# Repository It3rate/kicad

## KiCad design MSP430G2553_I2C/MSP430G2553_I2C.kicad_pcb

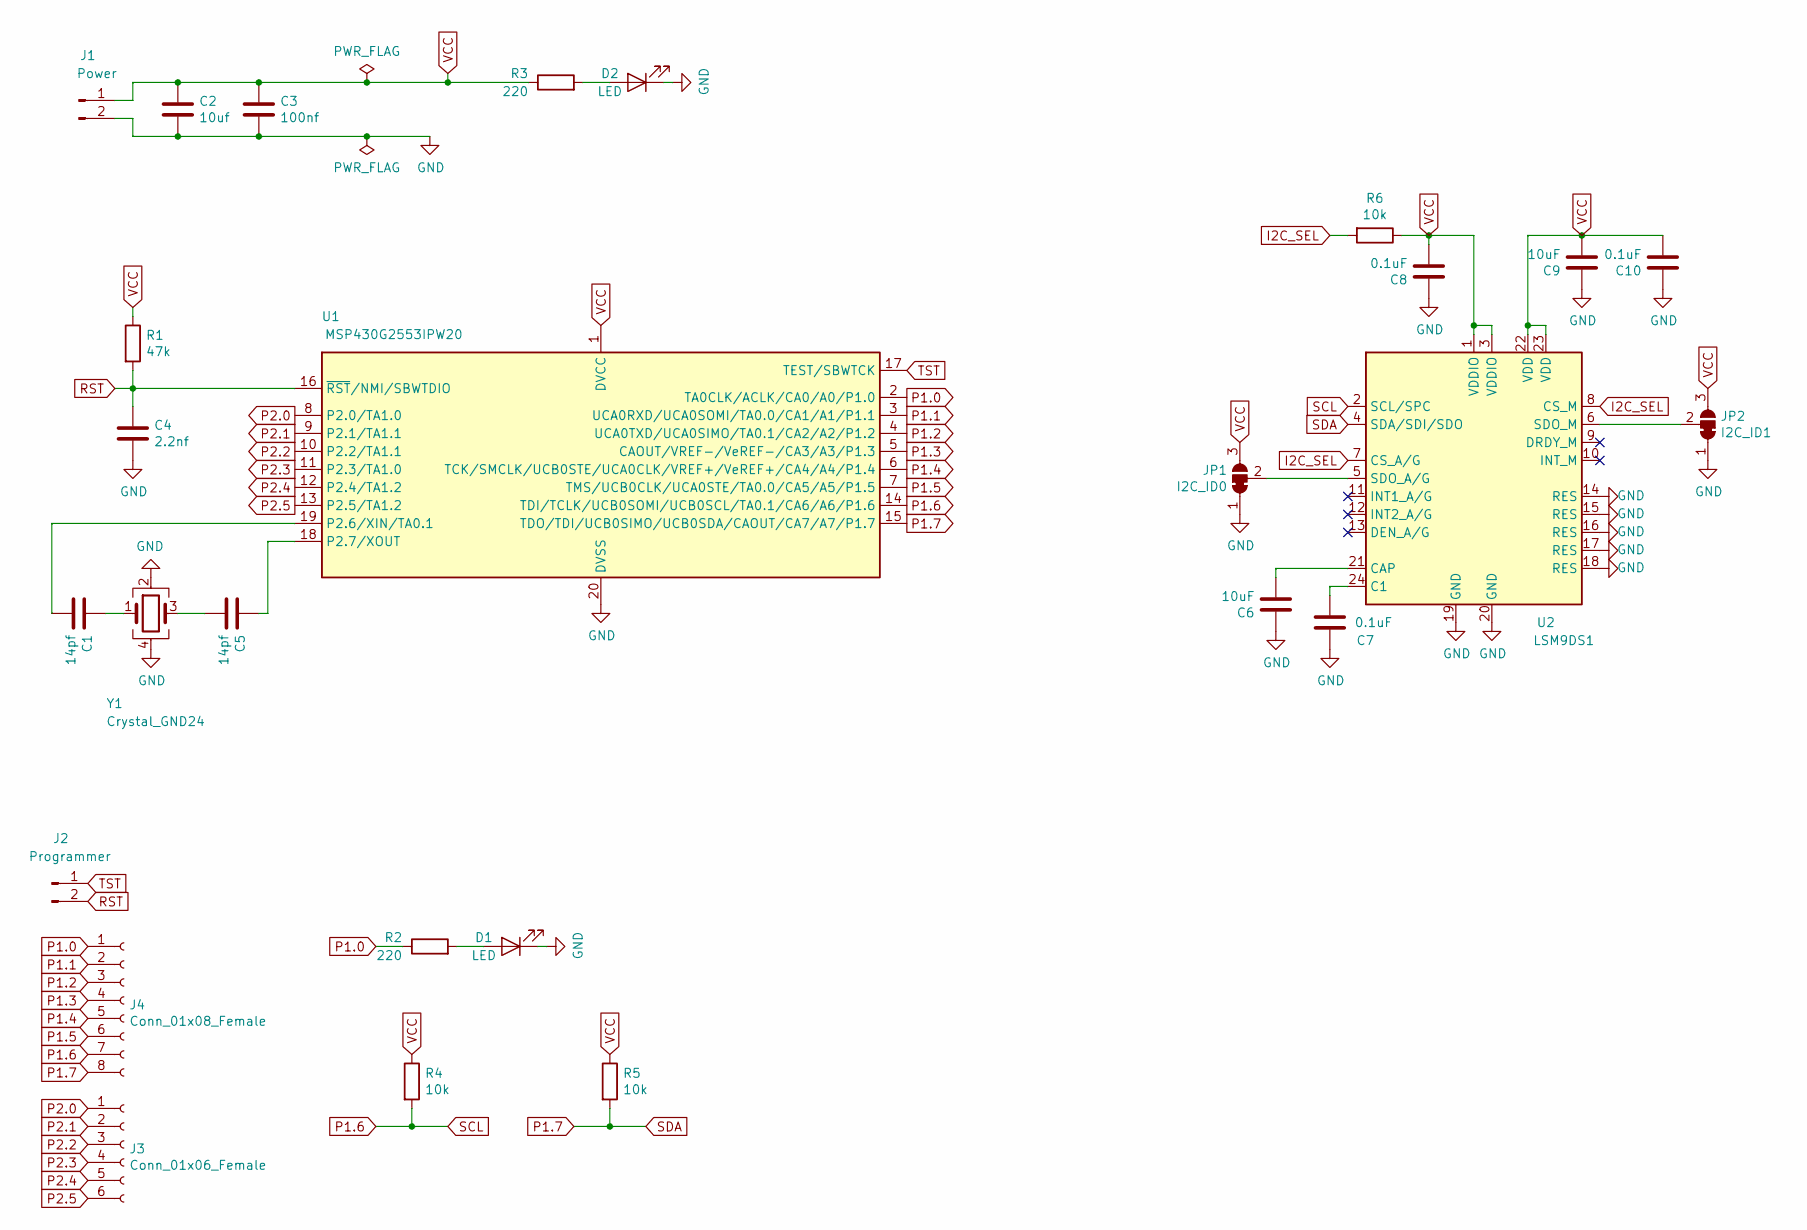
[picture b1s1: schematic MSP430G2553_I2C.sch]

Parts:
C1, C5: 14pf; thsmd_04_l_NH
C2: 10uf; thsmd_04_l_NH
C3: 100nf; thsmd_04_l_NH
C4: 2.2nf; thsmd_04_l_NH
C6, C9: 10uF; thsmd_04_l_NH
C7, C8, C10: 0.1uF; thsmd_04_l_NH
D1, D2: LED; LED_0805_2012Metric_Pad1.15x1.40mm_HandSolder
J1: Power; PinHeader_1x02_P2.54mm_Vertical
J2: Programmer; PinHeader_1x02_P2.54mm_Vertical
J3: Conn_01x06_Female; PinHeader_1x06_P2.54mm_Vertical
J4: Conn_01x08_Female; PinHeader_1x08_P2.54mm_Vertical
JP1: I2C_ID0; SolderJumper-3_P1.3mm_Bridged12_RoundedPad1.0x1.5mm
JP2: I2C_ID1; SolderJumper-3_P1.3mm_Bridged12_RoundedPad1.0x1.5mm
R1: 47k; thsmd_04_s_NH
R2, R3: 220; thsmd_04_s_NH
R4, R5, R6: 10k; thsmd_04_s_NH
U1: MSP430G2553IPW20; TSSOP-20_4.4x6.5mm_P0.65mm
U2: LSM9DS1; LGA-24L_3x3.5mm_P0.43mm
Y1: Crystal_GND24; Crystal_SMD_3225-4Pin_3.2x2.5mm_HandSoldering

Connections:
GND: C2.2, C3.2, C4.2, C6.1, C7.1, C8.1, C9.1, C10.1, D1.1 (K), D2.1 (K), J1.2, JP1.1 (A), JP2.1 (A), U1.20 (DVSS), U2.14 (RES), U2.15 (RES), U2.16 (RES), U2.17 (RES), U2.18 (RES), U2.19 (GND), U2.20 (GND), Y1.2, Y1.4
I2C_SEL: R6.2, U2.7 (CS_A/G), U2.8 (CS_M)
unnamed: C1.1, Y1.1
unnamed: C1.2, U1.19 (P2.6/XIN/TA0.1)
unnamed: C5.1, U1.18 (P2.7/XOUT)
unnamed: C5.2, Y1.3
unnamed: C6.2, U2.21 (CAP)
unnamed: C7.2, U2.24 (C1)
unnamed: D1.2 (A), R2.2
unnamed: D2.2 (A), R3.2
unnamed: JP1.2 (C), U2.5 (SDO_A/G)
unnamed: JP2.2 (C), U2.6 (SDO_M)
P1.0: J4.1, R2.1, U1.2 (TA0CLK/ACLK/CA0/A0/P1.0)
P1.1: J4.2, U1.3 (UCA0RXD/UCA0SOMI/TA0.0/CA1/A1/P1.1)
P1.2: J4.3, U1.4 (UCA0TXD/UCA0SIMO/TA0.1/CA2/A2/P1.2)
P1.3: J4.4, U1.5 (CAOUT/VREF-/VeREF-/CA3/A3/P1.3)
P1.4: J4.5, U1.6 (TCK/SMCLK/UCB0STE/UCA0CLK/VREF+/VeREF+/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)
P1.5: J4.6, U1.7 (TMS/UCB0CLK/UCA0STE/TA0.0/CA5/A5/P1.5)
P1.6: J4.7, R4.2, U1.14 (TDI/TCLK/UCB0SOMI/UCB0SCL/TA0.1/CA6/A6/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), U2.2 (SCL/SPC)
P1.7: J4.8, R5.2, U1.15 (TDO/TDI/UCB0SIMO/UCB0SDA/CAOUT/CA7/A7/P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), U2.4 (SDA/SDI/SDO)
P2.0: J3.1, U1.8 (P2.0/TA1.0)
P2.1: J3.2, U1.9 (P2.1/TA1.1)
P2.2: J3.3, U1.10 (P2.2/TA1.1)
P2.3: J3.4, U1.11 (P2.3/TA1.0)
P2.4: J3.5, U1.12 (P2.4/TA1.2)
P2.5: J3.6, U1.13 (P2.5/TA1.2)
RST: C4.1, J2.2, R1.2, U1.16 (~RST~/NMI/SBWTDIO)
TST: J2.1, U1.17 (TEST/SBWTCK)
VCC: C2.1, C3.1, C8.2, C9.2, C10.2, J1.1, JP1.3 (B), JP2.3 (B), R1.1, R3.1, R4.1, R5.1, R6.1, U1.1 (DVCC), U2.1 (VDDIO), U2.3 (VDDIO), U2.22 (VDD), U2.23 (VDD)

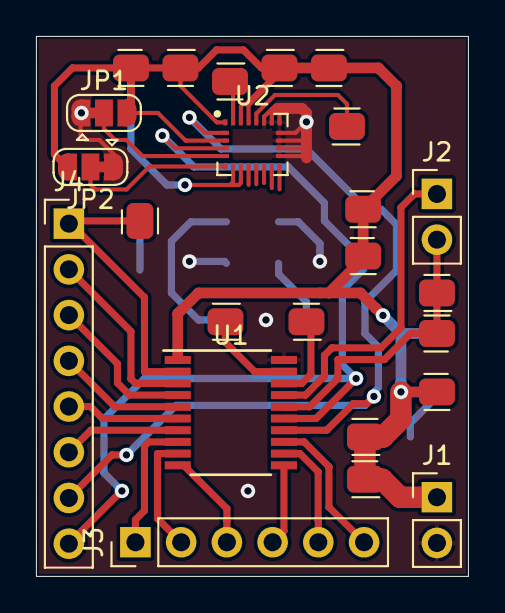
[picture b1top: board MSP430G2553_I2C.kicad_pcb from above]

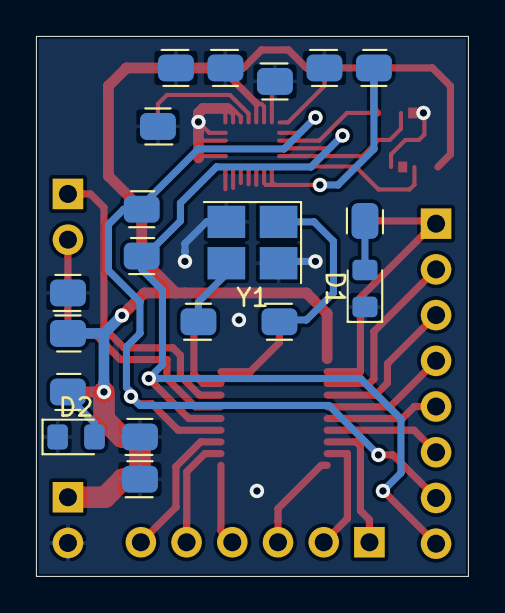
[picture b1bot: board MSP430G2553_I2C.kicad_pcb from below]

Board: 2 copper layers, 24.0 x 30.0 mm, 27 parts (10 on the bottom side), 29 nets.

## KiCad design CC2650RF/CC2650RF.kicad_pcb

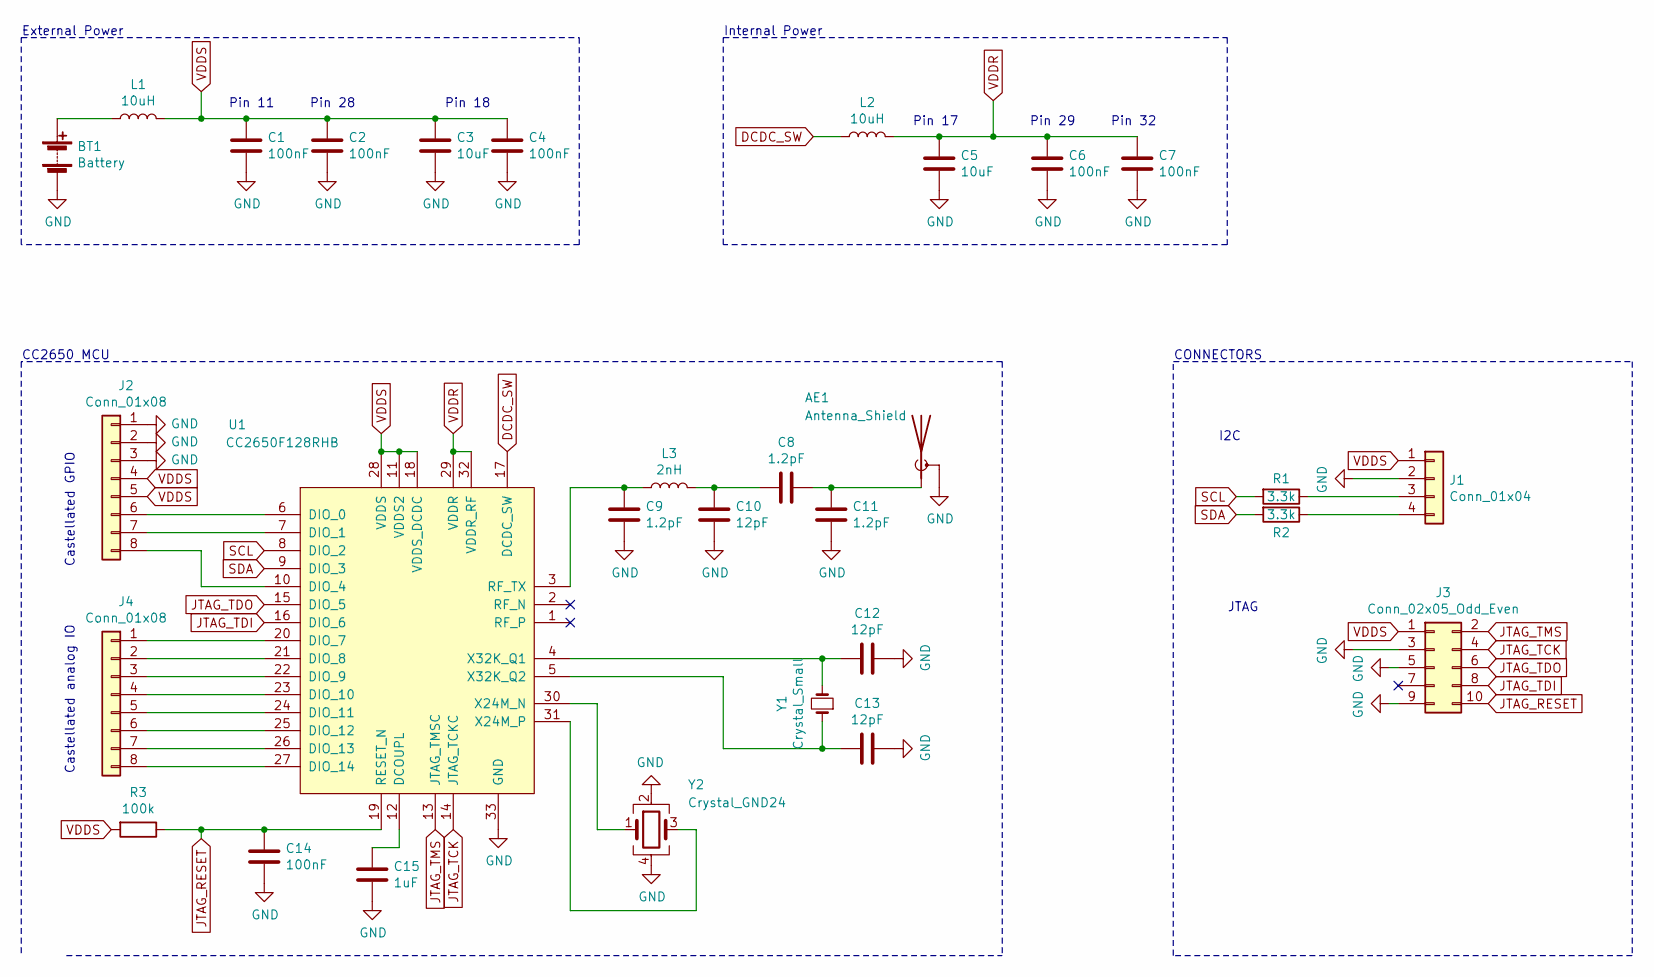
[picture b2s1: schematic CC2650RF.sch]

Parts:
AE1: Antenna_Shield; Texas_SWRA117D_2.4GHz_Right
BT1: Battery; PinSocket_1x02_P2.54mm_Vertical
C1, C2, C4, C6, C7, C14: 100nF; C_0603_1608Metric
C3, C5: 10uF; C_0603_1608Metric
C8, C9, C11: 1.2pF; C_0603_1608Metric
C10, C12, C13: 12pF; C_0603_1608Metric
C15: 1uF; C_0603_1608Metric
J1: Conn_01x04; PinSocket_1x04_P2.54mm_Vertical
J2, J4: Conn_01x08; Castallated_1x08_P2.54mm
J3: Conn_02x05_Odd_Even; PinHeader_2x05_P2.54mm_Vertical
L1, L2: 10uH; L_0603_1608Metric
L3: 2nH; L_0603_1608Metric
R1, R2: 3.3k; R_0603_1608Metric
R3: 100k; R_0603_1608Metric
U1: CC2650F128RHB; VQFN-32-1EP_5x5mm_P0.5mm_EP3.1x3.1mm
Y1: Crystal_Small; Crystal_SMD_MicroCrystal_MS3V-T1R
Y2: Crystal_GND24; Crystal_SMD_3225-4Pin_3.2x2.5mm

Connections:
DCDC_SW: L2.1, U1.17 (DCDC_SW)
GND: AE1.2 (Shield), BT1.2 (-), C1.2, C2.2, C3.2, C4.2, C5.2, C6.2, C7.2, C9.2, C10.2, C11.2, C12.2, C13.2, C14.2, C15.2, J1.2, J2.1, J2.2, J2.3, J3.3, J3.5, J3.9, U1.33 (GND), Y2.2, Y2.4
JTAG_RESET: C14.1, J3.10, R3.1, U1.19 (RESET_N)
JTAG_TCK: J3.4, U1.14 (JTAG_TCKC)
JTAG_TDI: J3.8, U1.16 (DIO_6)
JTAG_TDO: J3.6, U1.15 (DIO_5)
JTAG_TMS: J3.2, U1.13 (JTAG_TMSC)
unnamed: AE1.1 (A), C8.1, C11.1
unnamed: BT1.1 (+), L1.1
unnamed: C9.1, L3.1, U1.3 (RF_TX)
unnamed: C8.2, C10.1, L3.2
unnamed: C12.1, U1.4 (X32K_Q1), Y1.2
unnamed: C13.1, U1.5 (X32K_Q2), Y1.1
unnamed: C15.1, U1.12 (DCOUPL)
unnamed: J1.3, R1.1
unnamed: J1.4, R2.1
unnamed: J2.6, U1.6 (DIO_0)
unnamed: J2.7, U1.7 (DIO_1)
unnamed: J2.8, U1.10 (DIO_4)
unnamed: J4.1, U1.20 (DIO_7)
unnamed: J4.2, U1.21 (DIO_8)
unnamed: J4.3, U1.22 (DIO_9)
unnamed: J4.4, U1.23 (DIO_10)
unnamed: J4.5, U1.24 (DIO_11)
unnamed: J4.6, U1.25 (DIO_12)
unnamed: J4.7, U1.26 (DIO_13)
unnamed: J4.8, U1.27 (DIO_14)
unnamed: U1.30 (X24M_N), Y2.1
unnamed: U1.31 (X24M_P), Y2.3
SCL: R1.2, U1.8 (DIO_2)
SDA: R2.2, U1.9 (DIO_3)
VDDR: C5.1, C6.1, C7.1, L2.2, U1.29 (VDDR), U1.32 (VDDR_RF)
VDDS: C1.1, C2.1, C3.1, C4.1, J1.1, J2.4, J2.5, J3.1, L1.2, R3.2, U1.11 (VDDS2), U1.18 (VDDS_DCDC), U1.28 (VDDS)

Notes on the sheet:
Castellated GPIO
Castellated analog IO
CC2650 MCU
Pin 29
Pin 32
Pin 17
Pin 11
Pin 28
Pin 18
External Power
Internal Power
CONNECTORS
I2C
JTAG

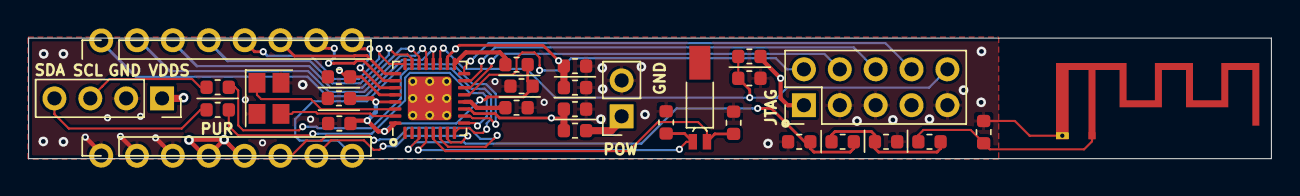
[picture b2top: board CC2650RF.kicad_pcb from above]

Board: 4 copper layers, 88.0 x 8.5 mm, 30 parts (0 on the bottom side), 33 nets.

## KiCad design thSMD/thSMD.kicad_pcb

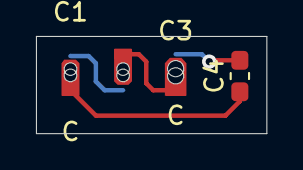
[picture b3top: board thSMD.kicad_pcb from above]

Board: 2 copper layers, 12.8 x 5.4 mm, 4 parts (1 on the bottom side), 4 nets.

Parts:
C1, C2: C; 0603_1
C3: C; 0603_2
C4: C; C_0603_1608Metric_Pad1.05x0.95mm_HandSolder

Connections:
+3V3: C1.1, C4.1
GND: C3.2, C4.2
unnamed: C1.2, C2.1
unnamed: C2.2, C3.1

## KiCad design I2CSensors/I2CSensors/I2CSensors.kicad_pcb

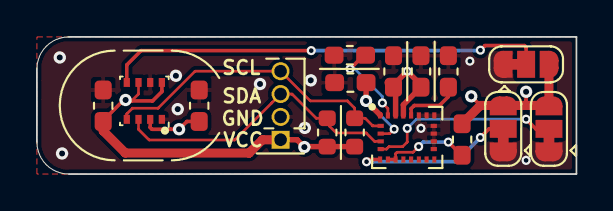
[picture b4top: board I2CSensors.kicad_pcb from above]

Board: 4 copper layers, 30.0 x 7.6 mm, 16 parts (0 on the bottom side), 10 nets.

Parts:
C1, C2, C4, C5, C7: 100nF; C_0603_1608Metric_Pad1.05x0.95mm_HandSolder
C3: 10nF; C_0603_1608Metric_Pad1.05x0.95mm_HandSolder
C6: 10uF; C_0603_1608Metric_Pad1.05x0.95mm_HandSolder
J1: Conn_01x04_Male; PinSocket_1x04_P1.27mm_Vertical
JP1, JP2, JP3: SolderJumper_3_Bridged12; SolderJumper-3_P1.3mm_Bridged12_RoundedPad1.0x1.5mm
R1, R2: DNM; R_0603_1608Metric
R3: 10k; R_0603_1608Metric_Pad1.05x0.95mm_HandSolder
U1: BME280; Bosch_LGA-8_2.5x2.5mm_P0.65mm_ClockwisePinNumbering
U2: LSM9DS1; LGA-24L_3x3.5mm_P0.43mm

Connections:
GND: C1.2, C2.2, C3.1, C4.1, C5.2, C6.2, C7.2, J1.2, JP1.1, JP2.1, JP3.1, U1.1, U1.7, U2.14, U2.15, U2.16, U2.17, U2.18, U2.19, U2.20
I2C_SEL: R3.1, U2.7, U2.8
unnamed: C3.2, U2.21
unnamed: C4.2, U2.24
unnamed: JP1.2, U1.5
unnamed: JP2.2, U2.5
unnamed: JP3.2, U2.6
SCL: J1.4, R1.1, U1.4, U2.2
SDA: J1.3, R2.1, U1.3, U2.4
VCC: C1.1, C2.1, C5.1, C6.1, C7.1, J1.1, JP1.3, JP2.3, JP3.3, R1.2, R2.2, R3.2, U1.2, U1.6, U1.8, U2.1, U2.3, U2.22, U2.23

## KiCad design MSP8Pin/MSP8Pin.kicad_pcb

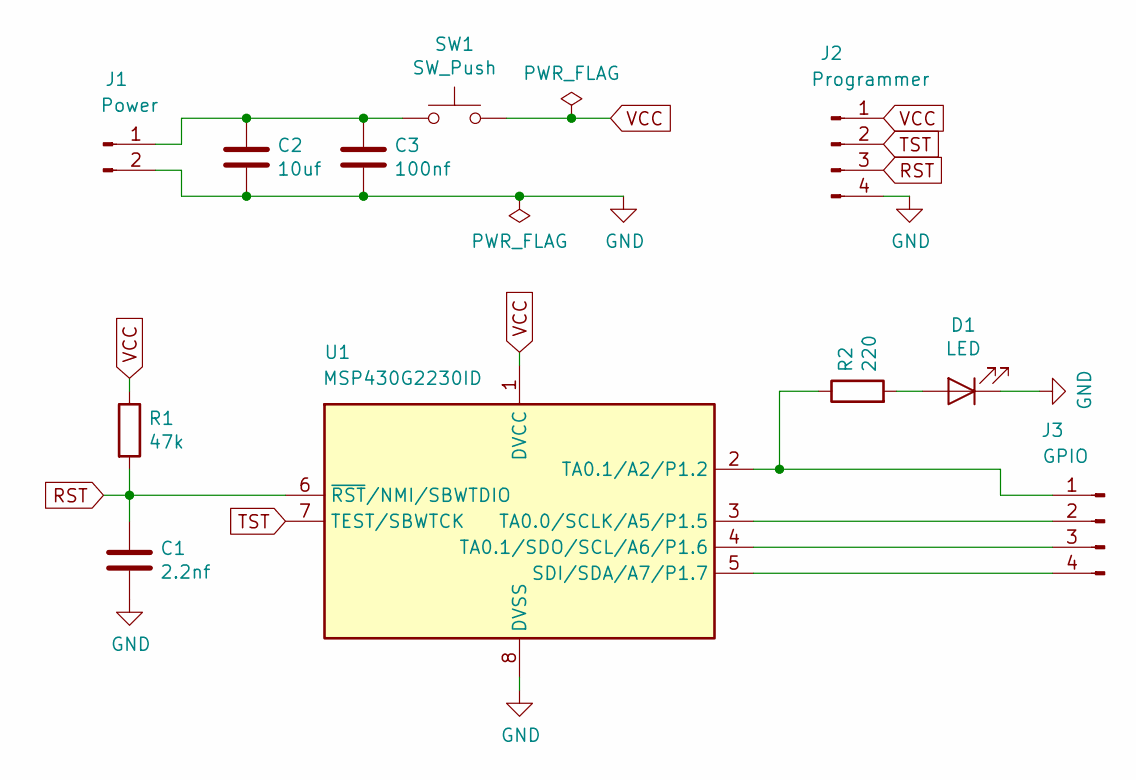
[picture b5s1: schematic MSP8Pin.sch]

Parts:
C1: 2.2nf; 0603_2L
C2: 10uf; 0603_2L
C3: 100nf; 0603_2L
D1: LED; LED_1206_3216Metric
J1: Power; PinHeader_1x02_P2.00mm_Vertical
J2: Programmer; PinHeader_1x04_P2.00mm_Vertical_BCu
J3: GPIO; PinHeader_1x04_P2.00mm_Vertical_BCu
R1: 47k; 0603_1L
R2: 220; 0603_1L
SW1: SW_Push; SW_Push_1P1T_NO_6x6mm_H9.5mm
U1: MSP430G2230ID; SOIC-8_3.9x4.9mm_P1.27mm

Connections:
GND: C1.2, C2.2, C3.2, D1.1 (K), J1.2, J2.4, U1.8 (DVSS)
unnamed: C2.1, C3.1, J1.1, SW1.1
unnamed: D1.2 (A), R2.2
unnamed: J3.1, R2.1, U1.2 (TA0.1/A2/P1.2)
unnamed: J3.2, U1.3 (TA0.0/SCLK/A5/P1.5)
unnamed: J3.3, U1.4 (TA0.1/SDO/SCL/A6/P1.6)
unnamed: J3.4, U1.5 (SDI/SDA/A7/P1.7)
RST: C1.1, J2.3, R1.2, U1.6 (~RST~/NMI/SBWTDIO)
TST: J2.2, U1.7 (TEST/SBWTCK)
VCC: J2.1, R1.1, SW1.2, U1.1 (DVCC)

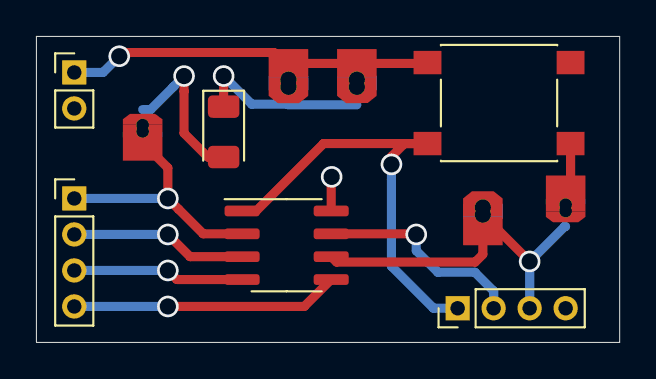
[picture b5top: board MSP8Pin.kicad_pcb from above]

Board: 2 copper layers, 32.4 x 17.0 mm, 11 parts (0 on the bottom side), 10 nets.

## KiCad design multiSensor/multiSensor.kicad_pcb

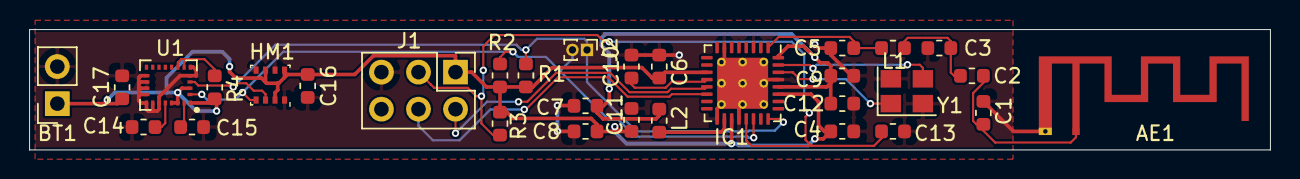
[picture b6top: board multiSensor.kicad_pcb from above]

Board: 2 copper layers, 85.1 x 8.3 mm, 31 parts (0 on the bottom side), 18 nets.

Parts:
AE1: Antenna_Shield; Texas_SWRA117D_2.4GHz_Right
BT1: Battery_Cell; PinSocket_1x02_P2.54mm_Vertical
C1, C2, C5: 1.2pF; C_0603_1608Metric
C3: 12pF; C_0603_1608Metric
C4, C6, C9, C11, C12, C15, C16, C17: 0.1uF; C_0603_1608Metric
C7, C8: 10uF; C_0603_1608Metric
C10: 1uF; C_0603_1608Metric
C13: 100nF; C_0603_1608Metric
C14: 10nF; C_0603_1608Metric
HM1: BME280; Bosch_LGA-8_2.5x2.5mm_P0.65mm_ClockwisePinNumbering
IC1: CC2650F128RSMT; VQFN-32-1EP_5x5mm_P0.5mm_EP3.5x3.5mm_ThermalVias
J1: JTAG; PinHeader_2x03_P2.54mm_Vertical
J2: Conn_01x02_Male; PinHeader_1x02_P1.00mm_Vertical
L1: 2nH; L_0603_1608Metric
L2: 10uH; L_0603_1608Metric
R1, R2: 4.7k; R_0603_1608Metric
R3: 102k; R_0603_1608Metric
R4: 10k; R_0603_1608Metric
U1: LSM9DS1; LGA-24L_3x3.5mm_P0.43mm
Y1: Crystal_GND24; Crystal_SMD_3225-4Pin_3.2x2.5mm

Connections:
DCDC_SW: IC1.18, L2.1
GND: AE1.2, BT1.2, C1.2, C3.1, C4.2, C5.1, C6.2, C7.2, C8.2, C9.2, C10.2, C11.2, C12.2, C13.2, C14.2, C15.2, C16.2, C17.2, HM1.1, HM1.5, HM1.7, IC1.3, IC1.7, IC1.17, IC1.20, IC1.29, IC1.33, J1.5, U1.5, U1.6, U1.14, U1.15, U1.16, U1.17, U1.18, U1.19, U1.20, Y1.2, Y1.4
I2C_SEL: R4.2, U1.7, U1.8
JTAG_TCK: IC1.14, J1.4
JTAG_TMS: IC1.13, J1.2
unnamed: AE1.1, C1.1, C2.2
unnamed: C2.1, C3.2, L1.1
unnamed: C5.2, IC1.1, L1.2
unnamed: C10.1, IC1.12
unnamed: C14.1, U1.21
unnamed: C15.1, U1.24
unnamed: IC1.30, Y1.1
unnamed: IC1.31, Y1.3
SCL: HM1.4, IC1.22, J2.2, R2.1, U1.2
SDA: HM1.3, IC1.24, J2.1, R1.1, U1.4
VDDR: C7.1, C9.1, C12.1, IC1.28, IC1.32, L2.2
VDDS: BT1.1, C4.1, C6.1, C8.1, C11.1, C16.1, C17.1, HM1.2, HM1.6, HM1.8, IC1.11, IC1.19, IC1.27, J1.1, R1.2, R2.2, R3.2, R4.1, U1.1, U1.3, U1.22, U1.23
nRESET: C13.1, IC1.21, J1.3, R3.1

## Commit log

2020-05-30 initial kicad lib
2020-06-01 new msp board and array.
2020-06-01 Adjusted g2553.
2020-06-03 Added i2c accel to msp430.
